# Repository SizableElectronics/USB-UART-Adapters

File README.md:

# USB-UART-Adapters
We started our UART adapters project because we needed a good insolated adapter. It's somewhat uncommon and not cheap. Time to change that. Check out [sizableelectronics.com/uart-adapters](https://sizableelectronics.com/uart-adapters) for more information. All projekt files and schematics are open source under the **Apache License Version 3.0**.

## Common features of all 3 adapters
* Uses the CP2102 usb to serial ic. Driver is usually not needed on Windows 7/8/10, Mac OS X and Linux.
* All adapters comes with the standard FTDI order of pins on the serial side of the adapter. `GND, NC, VCC, TXD, RXD and NC`. The colors will also match. This layout is the most used layout. But not everyone uses it, please check your layout before pluggin anything in to prevent burning boards.
* All adapters uses the new USB type C connector. Futureprooofness. A type-C to type-A cable is included in the box.

## Short info about the adapters
There are going to exist three different UART adapters in out serie. This is some short info about the induviual adapters below. For more info, check out their's appropriate folders.

* **Serial Dog**
A normal USB to UART/Serial adapter. Delivers 3.3v power to target.

* **Serial Fox**
A USB to UART/Serial adapter that have a wide input range. Both 3.3V and 5V will work. The name Serial Fox comes from the fact that a Fox is very agile, almost like this adapter with the context of voltage levels.

* **Serial Hopper**
A fully insolated USB to UART/Serial adapter. Protects the target from the computer and the other way around in case something bad would to happen to any on them. The name Serial Hopper comes from the fact that a grasshopper jumps really long. Almost like the insolated signals going through the adapter.

## A comparison between the adapters
Serial Dog | Serial Fox | Serial Hopper
--- | --- | ---
USB 2.0 (12 Mbps) | USB 2.0 (12 Mbps) | USB 2.0 (12 Mbps)
USB powers target | Needs power from both ends | Needs power from both ends
3.3V Target levels | 2-6V Target levels | 3.3 or 5v Target levels
Not insulated | Voltlevel insulation | Fully electric insulation
Target Price $11.9 | Target Price $11.9 | Target Price $16.9

## License
Apache License Version 3.0

## Typical BOM
Amount | Part | Description | Pad(s) | Datasheet | Buy Link
--- | --- | --- | --- | --- | ---
1 | CP2102N-A01-GQFN28 | USB to UART IC | U1 | [Github](https://github.com/SizableElectronics/USB-UART-Adapters/raw/master/datasheets/cp2102.pdf) | [LCSC](https://lcsc.com/product-detail/USB_SILICON-LABS_CP2102N-A01-GQFN28_CP2102N-A01-GQFN28_C105167.html) [Digikey](https://www.digikey.se/product-detail/en/silicon-labs/CP2102N-A01-GQFN28/336-3694-ND/6012519)
1 | TYPE-C-31-M-12 | USB Type-C connector | CN1 | -- | [Aliexpress](https://www.aliexpress.com/item/100PCS-LOT-USB-connector-Type-C-3-1-Female-connector-16Pin-SMD-SMT-Type-with-4/32822609480.html) [LCSC](https://lcsc.com/product-detail/USB-Type-C_TYPE-C-31-M-12-Female-16P-SMD_C165948.html)
1 | 1x6 Header | 6-pin, angled, 2.54mm/0.1", smd, female | C1 | -- | [Alibaba](https://www.alibaba.com/product-detail/SMD-0-1-Right-Angle-6_60556277672.html)
1 | USBLC6-2SC6 | USB Protection IC | D1 | -- | [Digikey](https://www.digikey.se/product-detail/en/stmicroelectronics/USBLC6-2SC6/497-5235-1-ND/1121688)
1 | AZ1117H-3.3TRG1  | LDO, Stepdowns for 3V3 | U2 | [Github](https://github.com/SizableElectronics/USB-UART-Adapters/raw/master/datasheets/AZ1117-1139752.pdf) | [Mouser](https://www.mouser.se/ProductDetail/Diodes-Incorporated/AZ1117H-33TRG1?qs=5V6w%252be2aIqa3gA4GjxrsQQ==) [LCSC](https://lcsc.com/product-detail/Low-Dropout-Regulators-LDO_DIODES_AZ1117H-3-3TRG1_AZ1117H-3-3TRG1_C110474.html)
2 | BAT54S | Target protection diods | D2, D3 | -- | [LCSC](https://lcsc.com/product-detail/Schottky-Barrier-Diodes-SBD_NXP_BAT54S_BAT54S-215_C47546.html)
6 | 22R Resistor | 0402 | R1,R2,R5,R6,R7,R8 | -- | [LCSC](https://lcsc.com/product-detail/Chip-Resistor-Surface-Mount_22R-220-5_C93929.html)
1 | 47k5 Resistor | 0402, for config of CP2102N | R3 | -- | [LCSC](https://lcsc.com/product-detail/Chip-Resistor-Surface-Mount-UniOhm_Uniroyal-Elec-0402WGF4752TCE_C25896.html)
1 | 22k1 Resistor | 0402, for config of CP2102N | R4 | -- | [LCSC](https://lcsc.com/product-detail/Chip-Resistor-Surface-Mount-UniOhm_Uniroyal-Elec-0402WGF2212TCE_C43473.html)
3 | 680R Resistor | 0402 | R9,R10,R11 | -- | [LCSC](https://lcsc.com/product-detail/Chip-Resistor-Surface-Mount-UniOhm_Uniroyal-Elec-0402WGJ0681TCE_C25177.html)
1 | 3K3 Resistor  | 0402 | R12 | -- | [LCSC](https://lcsc.com/product-detail/Chip-Resistor-Surface-Mount_3-3KR-332-5_C102983.html)
4 | 100n Capacitor | 0402 | C2,C3,C4,C5 | -- | [LCSC](https://lcsc.com/product-detail/Multilayer-Ceramic-Capacitors-MLCC-SMD-SMT_muRata_GCM155R71C104KA55D_100nF-104-10-16V-Car-level_C85857.html)
1 | 10u Capacitor | 0603 | C6 | -- | [LCSC](https://lcsc.com/product-detail/Multilayer-Ceramic-Capacitors-MLCC-SMD-SMT_10uF-106-20-16V_C109457.html)
1 | 600Ω Inductor | 0603 | L1 | -- | [LCSC](https://lcsc.com/product-detail/Ferrite-Beads-And-Chips_600R-25-1-3A_C97000.html)
1 | Polyfuse | 1206 | F1 | -- | [LCSC](https://lcsc.com/product-detail/Surface-Mount-Fuses_Self-healing-fuse-500mA-15V_C146252.html)
1 | ORANGE LED | TX LED 0603 | D4 | -- | [LCSC](https://lcsc.com/product-detail/_FFC-1608YOXK-600H08_C108553.html)
1 | GREEN LED | POWER LED 0603 | D5 | -- | [LCSC](https://lcsc.com/product-detail/Light-Emitting-Diodes-LED_Emerald-SMDLED-500-1080mcd_C87326.html)
1 | YELLOW LED | RX LED 0603 | D6 | -- | [LCSC](https://lcsc.com/product-detail/_FC-1608YXK-585F08_C89811.html)

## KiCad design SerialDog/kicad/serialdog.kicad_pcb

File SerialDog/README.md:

# Serial Dog
An Open Source USB to 3.3V UART adapter. Made with the help of EasyEDA. Use it as inpiration, build your own or buy a premade one from our **Amazon store** (comming soon). The project can also be found on our [public easyeda.com page](https://easyeda.com/webjocke/SerialDog).

## Schematic for Serial Dog v0.1

## How is Serial Dog different from the other Serial adapters?
Serial Dog Power the target though it's USB connection, which none of the other adapters in our lineup do. We have rated the output power to 500mAh, which a normal USB 2.0 port on a computer can provide. This also has a fixed output voltage at **3.3V**, both for the ouput power and for the signal pins.

## BOM
Amount | Part | Description | Pad(s) | Datasheet | Buy Link
--- | --- | --- | --- | --- | ---
1 | CP2102N-A01-GQFN28 | USB to UART IC | U1 | [Github](https://github.com/SizableElectronics/USB-UART-Adapters/raw/master/datasheets/cp2102.pdf) | [LCSC](https://lcsc.com/product-detail/USB_SILICON-LABS_CP2102N-A01-GQFN28_CP2102N-A01-GQFN28_C105167.html) [Digikey](https://www.digikey.se/product-detail/en/silicon-labs/CP2102N-A01-GQFN28/336-3694-ND/6012519)
1 | TYPE-C-31-M-12 | USB Type-C connector | CN1 | -- | [Aliexpress](https://www.aliexpress.com/item/100PCS-LOT-USB-connector-Type-C-3-1-Female-connector-16Pin-SMD-SMT-Type-with-4/32822609480.html) [LCSC](https://lcsc.com/product-detail/USB-Type-C_TYPE-C-31-M-12-Female-16P-SMD_C165948.html)
1 | 1x6 Header | 6-pin, angled, 2.54mm/0.1", smd, female | C1 | -- | [Alibaba](https://www.alibaba.com/product-detail/SMD-0-1-Right-Angle-6_60556277672.html)
1 | USBLC6-2SC6 | USB Protection IC | D1 | -- | [Digikey](https://www.digikey.se/product-detail/en/stmicroelectronics/USBLC6-2SC6/497-5235-1-ND/1121688)
1 | AZ1117H-3.3TRG1  | LDO, Stepdowns for 3V3 | U2 | [Github](https://github.com/SizableElectronics/USB-UART-Adapters/raw/master/datasheets/AZ1117-1139752.pdf) | [Mouser](https://www.mouser.se/ProductDetail/Diodes-Incorporated/AZ1117H-33TRG1?qs=5V6w%252be2aIqa3gA4GjxrsQQ==) [LCSC](https://lcsc.com/product-detail/Low-Dropout-Regulators-LDO_DIODES_AZ1117H-3-3TRG1_AZ1117H-3-3TRG1_C110474.html)
2 | BAT54S | Target protection diods | D2, D3 | -- | [LCSC](https://lcsc.com/product-detail/Schottky-Barrier-Diodes-SBD_NXP_BAT54S_BAT54S-215_C47546.html)
6 | 22R Resistor | 0402 | R1,R2,R5,R6,R7,R8 | -- | [LCSC](https://lcsc.com/product-detail/Chip-Resistor-Surface-Mount_22R-220-5_C93929.html)
1 | 47k5 Resistor | 0402, for config of CP2102N | R3 | -- | [LCSC](https://lcsc.com/product-detail/Chip-Resistor-Surface-Mount-UniOhm_Uniroyal-Elec-0402WGF4752TCE_C25896.html)
1 | 22k1 Resistor | 0402, for config of CP2102N | R4 | -- | [LCSC](https://lcsc.com/product-detail/Chip-Resistor-Surface-Mount-UniOhm_Uniroyal-Elec-0402WGF2212TCE_C43473.html)
3 | 680R Resistor | 0402 | R9,R10,R11 | -- | [LCSC](https://lcsc.com/product-detail/Chip-Resistor-Surface-Mount-UniOhm_Uniroyal-Elec-0402WGJ0681TCE_C25177.html)
1 | 3K3 Resistor  | 0402 | R12 | -- | [LCSC](https://lcsc.com/product-detail/Chip-Resistor-Surface-Mount_3-3KR-332-5_C102983.html)
4 | 100n Capacitor | 0402 | C2,C3,C4,C5 | -- | [LCSC](https://lcsc.com/product-detail/Multilayer-Ceramic-Capacitors-MLCC-SMD-SMT_muRata_GCM155R71C104KA55D_100nF-104-10-16V-Car-level_C85857.html)
1 | 10u Capacitor | 0603 | C6 | -- | [LCSC](https://lcsc.com/product-detail/Multilayer-Ceramic-Capacitors-MLCC-SMD-SMT_10uF-106-20-16V_C109457.html)
1 | 600Ω Inductor | 0603 | L1 | -- | [LCSC](https://lcsc.com/product-detail/Ferrite-Beads-And-Chips_600R-25-1-3A_C97000.html)
1 | Polyfuse | 1206 | F1 | -- | [LCSC](https://lcsc.com/product-detail/Surface-Mount-Fuses_Self-healing-fuse-500mA-15V_C146252.html)
1 | ORANGE LED | TX LED 0603 | D4 | -- | [LCSC](https://lcsc.com/product-detail/_FFC-1608YOXK-600H08_C108553.html)
1 | GREEN LED | POWER LED 0603 | D5 | -- | [LCSC](https://lcsc.com/product-detail/Light-Emitting-Diodes-LED_Emerald-SMDLED-500-1080mcd_C87326.html)
1 | YELLOW LED | RX LED 0603 | D6 | -- | [LCSC](https://lcsc.com/product-detail/_FC-1608YXK-585F08_C89811.html)

## Files
We have a specific folder for different versions of the adapters. This readme will always reflect the latest version. There is a schematic, layout images, BOM file, some pictures and the gerber files for production.

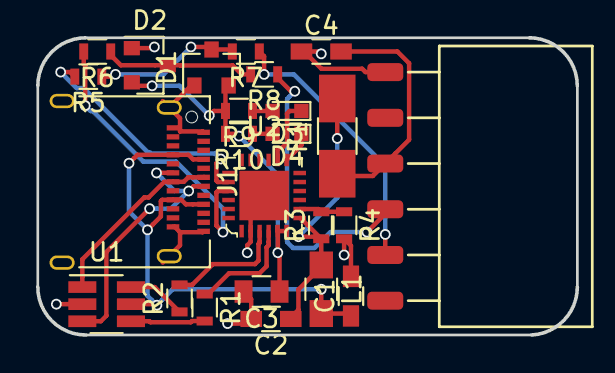
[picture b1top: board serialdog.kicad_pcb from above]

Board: 2 copper layers, 30.0 x 16.5 mm, 24 parts (0 on the bottom side), 22 nets.

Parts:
C1, C2, C4: 1u; R_0603_HandSoldering
C3: 1u; C_0805
D1, D2: BAT54S; SOT-23
D3, D4: LED; LED_0603
F1: Polyfuse_Small; Fuse_SMD1206_HandSoldering
J1: Connector:USB_C_Receptacle; USB_C_Receptacle_Amphenol_12401610E4-2A
J2: 1x6_2.54_smd_header; 1x6 header female smd
L1: Ferrite_Bead; R_0805_HandSoldering
R1, R2, R5, R6, R7, R8: 22; R_0603
R3: 22k; R_0603
R4: 47k; R_0603
R9, R10: 1k; R_0603
U1: USBLC6-2SC6; SOT-23-6_Handsoldering
U2: Interface_USB:CP2102N-A01-GQFN24; WQFN-24-1EP_4x4mm

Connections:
/REGIN: C2.1, F1.2, L1.1, R3.1, U2.7
/RX: D1.3, R5.1, R7.2
/TX: D2.3, R6.1, R8.2
/VBUS: C1.1, J1.A4, J1.A9, J1.B4, J1.B9, L1.2, U1.5
/VOUT: C4.2, F1.1, J2.3
GND: C1.2, C2.2, C3.2, C4.1, D1.1, D2.1, J1.A1, J1.A12, J1.B1, J1.B12, J1.S1, J2.1, R4.2, U1.2, U2.2, U2.25
unnamed: C3.1, D1.2, D2.2, R9.2, R10.2, U2.5, U2.6
unnamed: D3.1, U2.14
unnamed: D3.2, R9.1
unnamed: D4.1, U2.13
unnamed: D4.2, R10.1
unnamed: J1.A6, J1.B6, U1.1
unnamed: J1.A7, J1.B7, U1.3
unnamed: J2.4, R8.1
unnamed: J2.5, R7.1
unnamed: R1.1, U2.4
unnamed: R1.2, U1.4
unnamed: R2.1, U1.6
unnamed: R2.2, U2.3
unnamed: R3.2, R4.1, U2.8
unnamed: R5.2, U2.20
unnamed: R6.2, U2.21

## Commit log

2018-06-02 readme
2018-06-02 Added a basic folder structure and some partslist
2018-06-02 Updated Readme and added datasheet for cp2101
2018-06-04 Added cp2102 datasheet
2018-06-04 Added a ton of datasheets
2018-06-04 Datasheet of buffer
2018-06-04 Added datasheet and updated SerialBear partslist
2018-06-05 Fixed speeling error
2018-06-05 removed partlist file and created a readme instead
2018-06-05 Added/updated the git ignore
2018-06-05 Spell checking
2018-06-05 Added a few kicad schematic components
2018-06-05 Started on the serialdog schematic, needs more work
2018-06-07 Tried to start on the pcb layout
2018-06-09 Kicad v5, pcb design started
2018-06-10 Made first pcb layout draft
2018-06-20 Added
2018-07-04 Updated the readme and removed old files
2018-07-04 Updated readme's
2018-07-15 Create LICENSE
2018-08-01 Changes some Serial Dog information
2018-08-12 Added Some of the images and gerber/schematic/layout files
2018-08-12 Added schematic to readme file
2018-08-12 Replaced image
2018-08-13 Sorted the bom list and added a web version of the nice image
2018-08-13 Change a alt text of the image
2018-08-13 Fixed broken link
2018-08-13 New image
2018-08-13 Added a value to the table
2018-08-13 Added a value again xD
2018-08-13 Fixed some text
2018-12-11 Removed a lot of old files
